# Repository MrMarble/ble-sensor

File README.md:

# BLE Temperature and humidity sensor

### ⚠️ Work in Progress
I'm still playing around with the layout, it might not work, don't try to use it yet **but** if you know about electronics feel free to review 😄

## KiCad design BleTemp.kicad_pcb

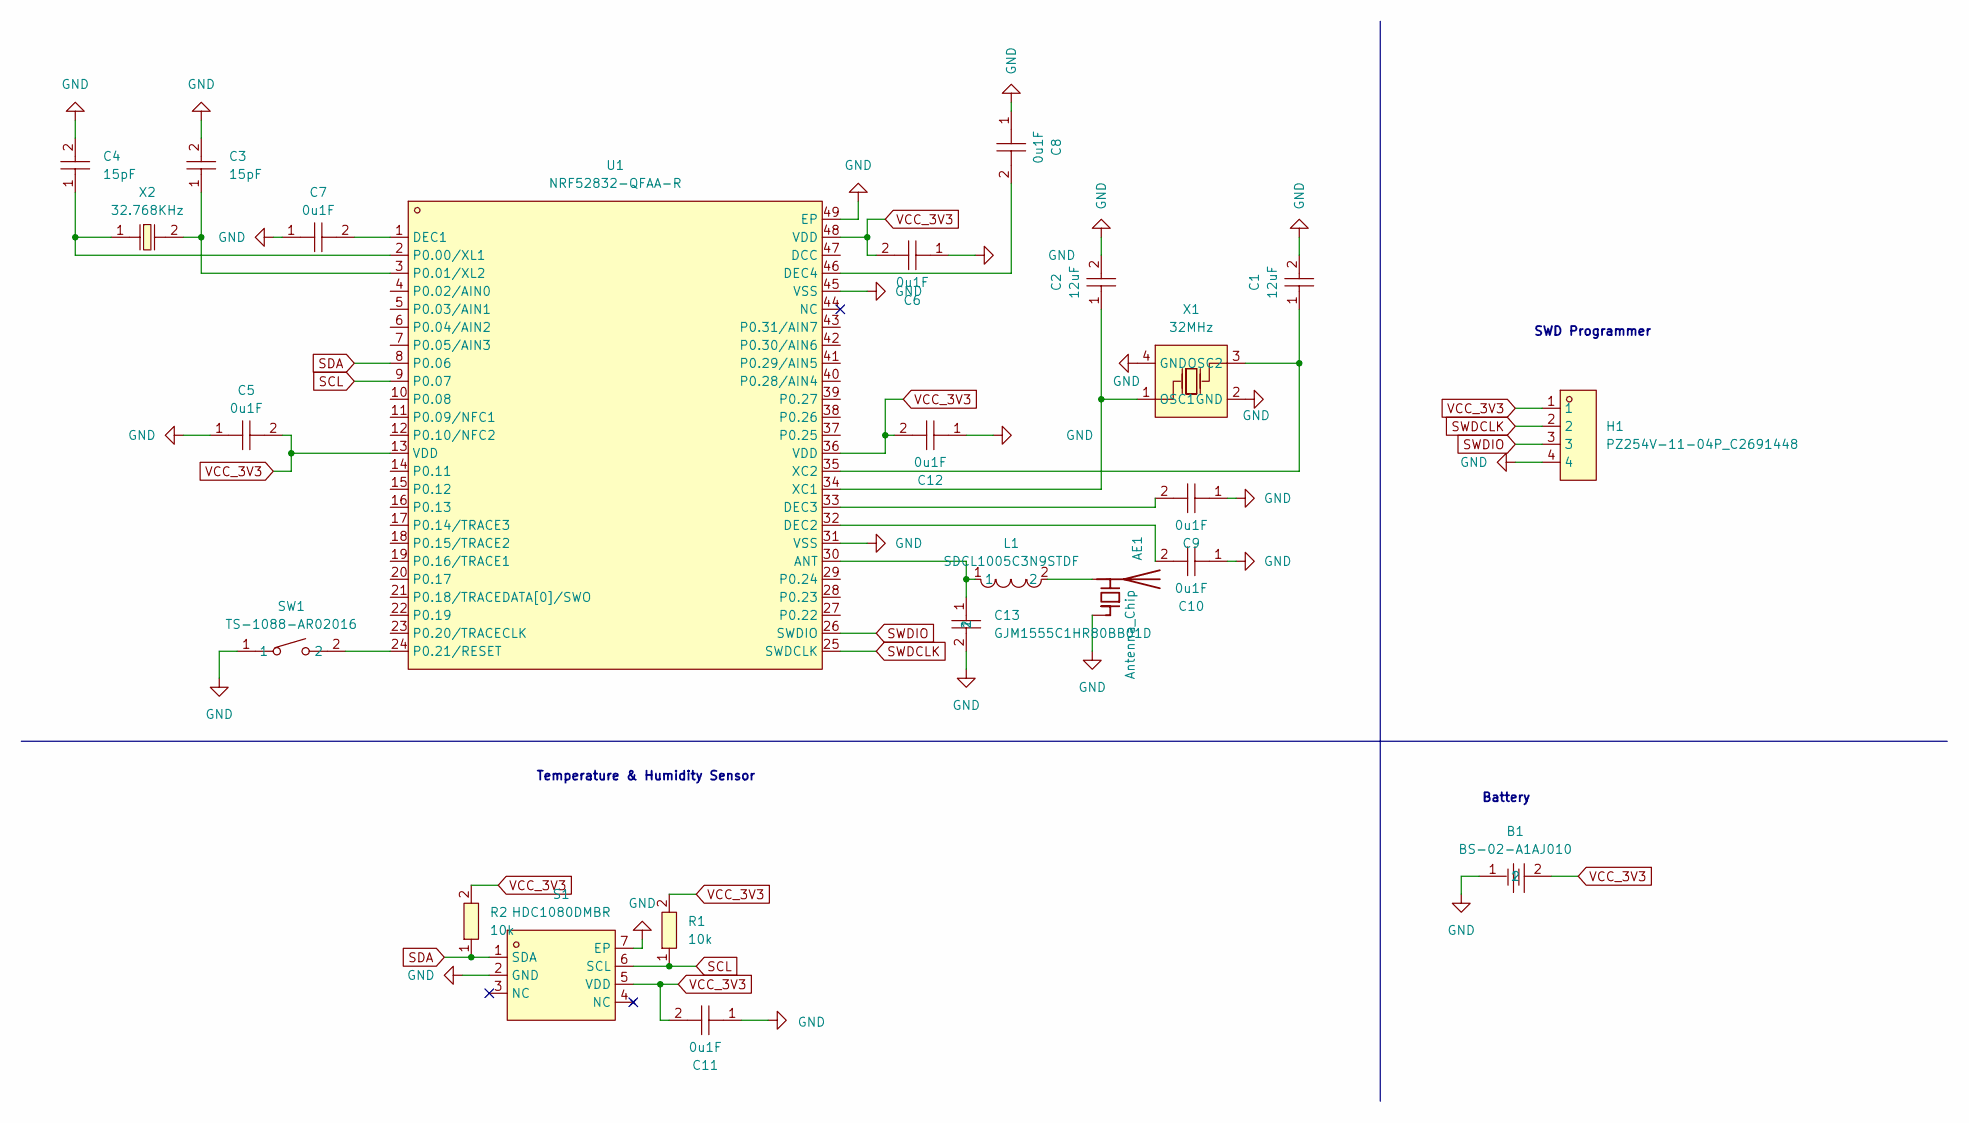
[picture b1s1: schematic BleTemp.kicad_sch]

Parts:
AE1: Antenna_Chip; ANT-F-1-2.4G-1.6MM-FR4-WCH
B1: BS-02-A1AJ010; BAT-TH_BS-02-A1AJ010; LCSC Part C5239862
C1, C2: 12uF; C0402; LCSC Part C1547
C3, C4: 15pF; C0402; LCSC Part C1548
C5, C6, C7, C8, C9, C10, C11, C12: 0u1F; C0402; LCSC Part C1525
C13: GJM1555C1HR80BB01D; C0402; LCSC Part C76915
H1: PZ254V-11-04P_C2691448; HDR-TH_4P-P2.54-V-M; LCSC Part C2691448
L1: SDCL1005C3N9STDF; L0402; LCSC Part C14033
R1, R2: 10k; R0603; LCSC Part C25804
S1: HDC1080DMBR; SENSOR-SMD_HDC1080DMBR; LCSC Part C82227
SW1: TS-1088-AR02016; SW-SMD_L3.9-W3.0-P4.45; LCSC Part C720477
U1: NRF52832-QFAA-R; QFN-48_L6.0-W6.0-P0.40-BL-EP3.8; LCSC Part C77540
X1: 32MHz; CRYSTAL-SMD_4P-L3.2-W2.5-BL; LCSC Part C9009
X2: 32.768KHz; FC-135R_L3.2-W1.5; LCSC Part C32346

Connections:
GND: AE1.1 (FEED), B1.1, C1.2, C2.2, C3.2, C4.2, C5.1, C6.1, C7.1, C8.1, C9.1, C10.1, C11.1, C12.1, C13.2, H1.4, S1.2 (GND), S1.7 (EP), SW1.1, U1.31 (VSS), U1.45 (VSS), U1.49 (EP), X1.2 (GND), X1.4 (GND); also elsewhere on the board
unnamed 1: AE1.2 (PCB_Trace), L1.2; also elsewhere on the board
unnamed: C13.1, L1.1, U1.30 (ANT)
unnamed: C7.2, U1.1 (DEC1)
unnamed: C10.2, U1.32 (DEC2)
unnamed: C9.2, U1.33 (DEC3)
unnamed: C8.2, U1.46 (DEC4)
unnamed: C4.1, U1.2 (P0.00/XL1), X2.1
unnamed: C3.1, U1.3 (P0.01/XL2), X2.2
unnamed 9: SW1.2, U1.24 (P0.21/RESET); also elsewhere on the board
unnamed: C2.1, U1.34 (XC1), X1.1 (OSC1)
unnamed: C1.1, U1.35 (XC2), X1.3 (OSC2)
SCL: R1.1, S1.6 (SCL), U1.9 (P0.07)
SDA: R2.1, S1.1 (SDA), U1.8 (P0.06)
SWDCLK: H1.2, U1.25 (SWDCLK)
SWDIO: H1.3, U1.26 (SWDIO)
VCC_3V3: B1.2, C5.2, C6.2, C11.2, C12.2, H1.1, R1.2, R2.2, S1.5 (VDD), U1.13 (VDD), U1.36 (VDD), U1.48 (VDD)

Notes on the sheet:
Battery
Temperature & Humidity Sensor
SWD Programmer

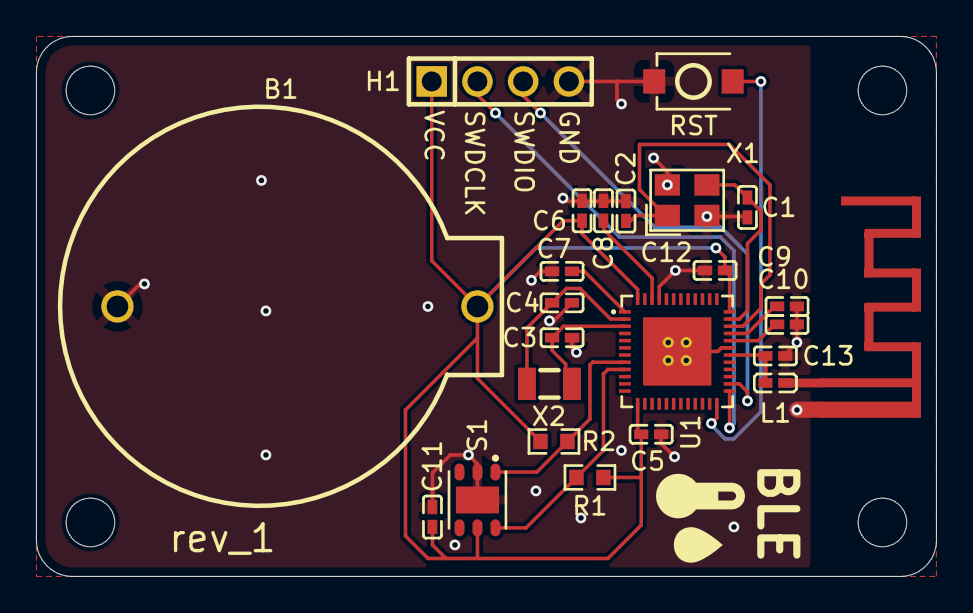
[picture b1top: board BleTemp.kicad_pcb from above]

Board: 2 copper layers, 50.0 x 30.0 mm, 24 parts (0 on the bottom side), 17 nets.

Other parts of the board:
ANT: Antenna_Chip; ANT-F-1-2.4G-1.6MM-FR4-WCH
RST: TS-1088-AR02016; SW-SMD_L3.9-W3.0-P4.45

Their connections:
GND: ANT.1 (FEED), RST.1; also elsewhere on the board
unnamed 1: ANT.2 (PCB_Trace); also elsewhere on the board
unnamed 9: RST.2; also elsewhere on the board

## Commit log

2025-08-29 connect antenna
2025-08-29 add copper zones
2025-08-29 add traces
2025-09-04 improve antenna connection
2025-09-04 Add 3D file
2025-09-04 Update gerber files
2025-09-04 untrack kicad files
2025-09-04 add basic readme
